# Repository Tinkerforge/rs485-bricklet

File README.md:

# rs485-bricklet
Communicates with RS485 devices

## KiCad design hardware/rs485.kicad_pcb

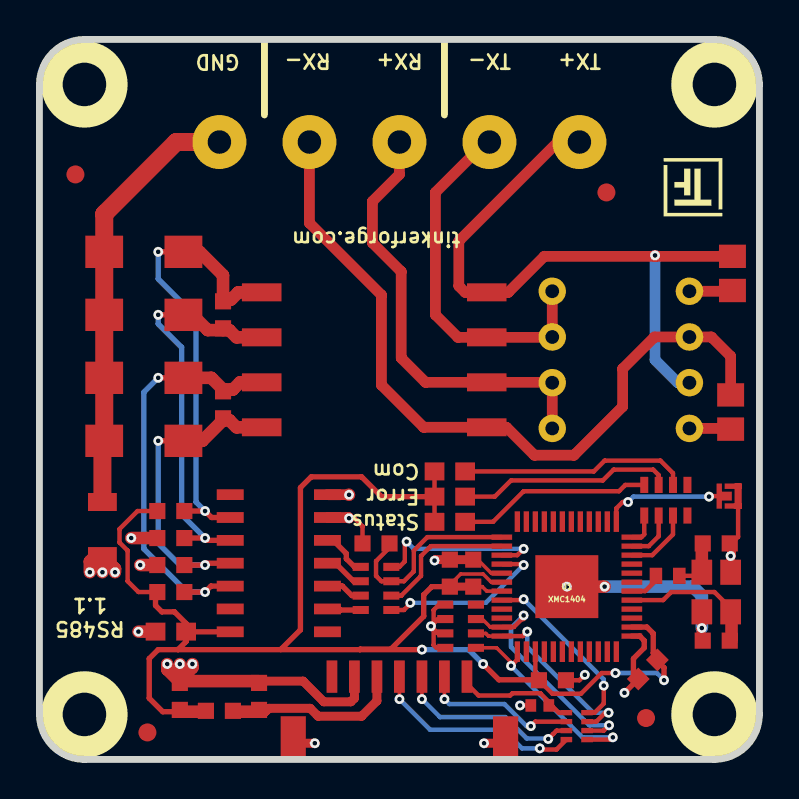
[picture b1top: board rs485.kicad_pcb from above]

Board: 2 copper layers, 40.0 x 40.0 mm, 51 parts (0 on the bottom side), 40 nets.

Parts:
C1, C2: 1uF; C0603F
C3, C4, C5: 100nF; C0603F
C6: 220nF; C0603F
C7: 100nF; C0603E
C8, C9: 10pF; C0603F
C101: 220pF; C0402F
D1: yellow; D0603E
D2: red; D0603E
D3: blue; D0603E
D4, D5, D6, D7: SMAJ24CA; DO-214AC
FB1: FILTER; R0603F
Fiducial_Mark: VAL**; Fiducial_Mark
Fiducial_Mark#2, Fiducial_Mark#3, Fiducial_Mark#4: VAL**; Fiducial_Mark
L1: WE-SL
P1: CON-SENSOR2
P2: BOOT; SolderJumper
P3: CONN_5; AKL_5_5
PTC1: 0ZCJ0016FF2E; C1206
R1, R2: 120; R0805E
R3, R5, R6, R8: 2.7k; R0603F
R4, R7: 2.2k; R0603F
R9: 0; R0402E
R101: 10k; R0603F
RP1: 1k; 0603X4
RP2, RP3: 10k; 0603X4
RP101: 82; 4X0402
SW1: SW_DIP_4; SW_DIP_4_THT
U1: XMC1404; QFN48-EP2
U2, U3, U4, U5: DRILL; DRILL_NP
U6: SP3491; SOIC-14_3.9x8.7mm_Pitch1.27mm
VAL: WEEE_7mm
VAL#2: CE_5mm
X1: 16MHz; CRYSTAL_3225

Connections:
485-D: RP2.4, U1.15
485-DE: R101.1, RP2.3, U1.13
485-R: RP2.1, U1.16
485-~REB: RP2.2, U1.14
Earth: D4.2, D5.2, D6.2, D7.2, P3.1, PTC1.1
GND: C1.1, C2.1, C3.2, C4.2, C5.2, C6.2, C7.1, C8.2, C9.2, C101.2, P1.2, P1.EP, P2.1, PTC1.2, R5.2, R8.2, R101.2, RP3.5, RP3.6, RP3.7, RP3.8, U1.17, U1.37, U1.EP, U6.6, U6.7, X1.3
unnamed: C1.2, FB1.1, P1.3
unnamed: C8.1, U1.41, X1.2
unnamed: C9.1, R9.2, X1.1
unnamed: C101.1, P1.7, RP101.5
unnamed: D1.2, RP1.2
unnamed: D2.2, RP1.3
unnamed: D3.2, RP1.4
unnamed: D4.1, L1.4, R4.2, R5.1, U6.11
unnamed: D5.1, L1.2, R7.2, R8.1, U6.10
unnamed: D6.1, L1.3, R3.2, R4.1, U6.12
unnamed: D7.1, L1.1, R6.2, R7.1, U6.9
unnamed: P1.4, RP101.8
unnamed: P1.5, RP101.7
unnamed: P1.6, RP101.6
unnamed: P2.2, U1.1
unnamed: R1.1, SW1.5
unnamed: R2.2, SW1.8
unnamed: R9.1, U1.42
unnamed: RP1.5, U1.48
unnamed: RP1.6, U1.47
unnamed: RP1.7, U1.46
unnamed: RP2.5, U6.5
unnamed: RP2.6, U6.4
unnamed: RP2.7, U6.3
unnamed: RP2.8, U6.2
RX: L1.6, P3.3, SW1.3, SW1.4
S-CLK: RP3.3, RP101.2, U1.23
S-CS: RP3.1, RP101.1, U1.25
S-MISO: RP101.4, U1.20
S-MOSI: RP3.2, RP101.3, U1.24
TX: L1.8, P3.5, R2.1, SW1.6
VCC: C2.2, C3.1, C4.1, C5.1, C6.1, C7.2, D1.1, D2.1, D3.1, FB1.2, R3.1, R6.1, U1.18, U1.19, U1.27, U1.38, U6.14
~RX: L1.5, P3.2, R1.2, SW1.7
~TX: L1.7, P3.4, SW1.1, SW1.2

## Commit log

2016-11-07 initial commit: change README
2016-11-11 routing and schematic finished, bottom markings missing
2016-11-11 add wee, ce logos, dip description, fiducials
2016-11-11 ordered first prototype
2016-11-15 add xmc1400 datasheet
2016-11-17 Add initial software implementation for RS485
    General half-duplex rx/tx wors, no TFP communication yet
2016-11-17 Add .gitignore
2016-11-22 Add implementation of first messages
2016-11-22 Add get uid bootloader function
2016-11-22 Add communication tick call
2016-11-22 Fix typo
2016-11-22 Add apply configuration prototype
2016-11-22 Add configuration enums and defines
2016-11-22 Add proper configuration and error/overrun error detection
2016-11-22 Add RXA interrupt and sort priorities properly
2016-11-22 specify crystal and capacitors
2016-11-22 Add led_flicker.c to Makefile
2016-11-22 Change priority back (RS485 only needs 3 levels)
2016-11-22 Add handling for red and yellow LED
    TODO: User LED configuration
2016-11-22 Use external oscillator
2016-11-23 Use communication callback utility function to handle callbacks
2016-11-25 Optimize tff irq handler
2016-11-25 Use error count instead of error flag, add led config
2016-11-25 Add error count and led status to struct
2016-11-25 Add API for led config and error count
2016-11-28 fix footprints
2016-11-28 Define max baudrate as 2000000 (we don't use the theoretical maximum)
2016-11-29 Add some test scripts
2016-11-29 add init
2016-11-29 Fix end of ringbuffer
2016-11-29 Add boot pad pin
2016-11-29 Add full-duplex support
2016-11-30 Use enumerate for flashing
2016-11-30 Changes in test scripts
2016-12-01 Add support for heartbeat led flicker
2016-12-02 Remove debug output
2016-12-02 Disable interrupts during buffer init
2016-12-08 Start version with 2.0.0
2016-12-08 Use clock calibration with external clock
2016-12-08 Simplify callback handling
2017-01-04 add comcu icon
2017-01-10 change bricklet connector to 7pole JST GH connector
2017-01-12 add pulldown resistors for SPI
2017-01-12 add pulldown for spi inputs, change via size
2017-01-12 change via diameter
2017-01-19 Add EEPROM emulation size
2017-01-19 Add bootloader eeprom flash read/write defines
2017-01-23 Fix include guard
2017-01-25 Add documentation related to Modbus
2017-02-03 Use O2 optimization for RS485
2017-02-07 add license file
2017-02-09 Implementation of Modbus slave read coils function. Note that this commit is not compatible with current Git brickv and bindings this will be fixed soon after timing changes are committed
2017-02-09 Add support for CCU4 based 3.5 char timer
2017-02-16 Implementation of Modbus read coils function
2017-02-21 Fix data type of read/write holding register functions
2017-02-22 Add support for Modbus write single coil function
2017-02-22 Add support for Modbus read single register function
2017-02-22 Add support for Modbus write single register function
2017-02-24 Add Modbus write multiple coils functionality
2017-02-27 Add Modbus function write multiple registers
2017-02-27 Modbus add read discrete inputs function
2017-02-28 Add Modbus function read input registers
2017-02-28 Support broadcast frame handling
2017-02-28 Fix broadcast message handling
2017-03-01 Get rid of apply_configuration() function which is not needed
2017-03-10 Adapt to bootloader LED flicker config change
2017-03-13 Use CRC16 with lookup-table
2017-04-06 Whitespace
2017-04-07 Adapt to API changes
    Add Master/Slave prefix to Modbus functions.
    Remove data parameters from Answer Write functions.
    Ensure that the normal RS485 functions do nothing in Modbus mode.
    Remove static modifier from local varaibles that don't need to be static.
2017-04-10 Broadcast for read requests are considered invalid
2017-04-10 Generate callbacks locally for broadcast write requests
2017-04-12 Add rx/tx information to allow for hald-fuplex bootstrapper flashing
2017-04-12 In slave mode write requests are answered by copying the request frame from the RX buffer
2017-04-12 Fix function parameter data type
2017-04-13 Adapt firmware for new bool array data type
2017-04-13 Use right variable
2017-04-19 Add streaming support for raw RS485 mode read/write functions
2017-04-19 bricklet-rs485: Initialize callback data
2017-04-19 Adjust streaming read callback handling
2017-04-20 Get rid of redundant count parameter
2017-04-20 Enhance error counting and timeout reporting
2017-04-21 Read function returns available data when read callback is disabled
2017-04-24 In case of a buffer overflow after reading and throwing away data instead of returning from the function continue reading as long as there is data available like in non-overflow case
2017-04-24 Ensure that in no situation unassigned values are returned through response
2017-05-02 Fix streaming read implementation
2017-05-05 Add 3d information
2017-05-05 Add 3d model: *.step & *.FCStd
2017-05-10 Fix write multiple registers endianness problem
2017-05-10 Get rid of redundant count parameter from write multiple coils/registers callbacks
2017-05-10 Change stream chunk data size to utilize all available space per packet
2017-05-10 bricklet-rs485: Change Modbus protocol level data addressing scheme
2017-05-15 Add loopback example in C and Python
2017-05-16 Make read callback to properly stream data
2017-05-17 Increase starting address for write single coil/register request callbacks
2017-05-17 Add C Modbus master and slave examples
2017-05-17 Use Modbus exception code constants
2017-05-17 Simplify Modbus master and slave mode C examples
2017-05-17 Add Modbus master and slave Python examples
2017-05-17 Add Modbus master and slave C# examples
2017-05-17 Add Modbus master and slave Ruby examples
2017-05-17 Add Modbus master and slave Java examples
2017-05-18 Fix comments
2017-05-18 Add Modbus master and slave PHP examples
2017-05-18 Add Modbus master and slave VB.NET examples
2017-05-19 Put rx and tx callback into ram for faster function call
2017-05-22 Add Modbus master and slave examples for Shell bindings
2017-05-22 Add Modbus master and slave Perl examples
2017-05-22 Add Modbus master and slave JavaScript examples
2017-05-22 Use 16 bit fifo trigger for rx interrupt
2017-05-22 Fix comment
2017-05-22 Move variable
2017-05-22 Use copy of pointer for interrupt (bettter efficiency)
2017-05-23 Fix C examples
2017-05-23 Add Modbus master and slave Delphi/Lazarus examples
2017-05-23 Fix Modbus master Ruby example
2017-05-23 Add loopback Ruby example
2017-05-24 Add Modbus master and slave MATLAB examples
2017-05-24 Add shell loopback example
2017-05-24 Fix Modbus master MATLAB example
2017-05-24 Add Modbus master and slave Octave examples
2017-05-24 Add PHP loopback example
2017-05-24 Add Perl loopback example
2017-05-24 Fix Modbus master and slave JavaScript web examples
2017-05-24 Add JavaScript loopback examples
2017-05-24 Fix loopback example comment
2017-05-24 Add Java loopback example
2017-05-24 Add C# loopback example
2017-05-24 Fix Java loopback example
2017-05-24 Add Delphi/Lazarus loopback example
2017-05-26 Fix Modbus master and slave Octave examples
2017-05-26 Fix Modbus Octave example type specifiers
2017-05-26 Add MATLAB and Octave loopback examples
2017-05-26 Add VB.NET loopback example
2017-05-26 Rename C# .NET examples
2017-06-01 c: Add missing string.h include
2017-06-01 c: Fix strndup for real now
2017-06-01 c: strndup not available with mingw32-gcc on Ubuntu 14.04
2017-06-02 Whitespace and typos
2017-06-06 Adapt examples to be more in line with the RS232 examples
    Also do some style unification.
2017-06-06 Swap mode constants
2017-06-14 php: Explode doesn't work with an empty delimiter
2017-06-23 perl: Fix array passing
2017-06-28 vbnet: Fix compile errors
2017-07-17 perl: Cleanup shared usage
2017-07-17 shell: Fix slave address in example
2017-07-17 perl: Fix shared warning
2017-07-24 examples: Add missing full-duplex configuration
2017-07-25 Add Mathematica examples
2017-07-25 Add LabVIEW examples
2017-07-26 add schematic file
2017-07-27 Update changelog
2017-08-24 Specify R9 to 0 Ohm
2017-08-30 Fix bug: starting address was not being adjusted for multi-chunk streams
2017-08-30 Fix version
2017-09-08 fix footprint silkscreen layers
2017-10-20 Java: Fix example
2017-11-17 delphi: Fix example
2017-11-17 delphi,javascript: Disable streaming example until streaming is fully supported
2017-11-30 @{function_camel_case_name}[
2017-11-30 Update examples from generator
2017-12-06 specify new rs485 biasing resistors
2017-12-07 mathematica: Also generate .nb files
2018-01-30 vbnet: Update print format
2018-02-19 javascript: Close div tag correctly
2018-02-20 Cleanup KiCad libraries config
    Ensure LibDir=kicad-libraries and LibName1=tinkerforge.
    Remove special library.
2018-02-22 delphi: Fix syntax error
2018-03-05 Remove unused flash-size define
2018-05-24 perl: Use strict in examples
2018-06-28 Fix readme
2018-07-11 Add Makefile with docker support
2018-07-11 Update directory structure and build instructions
2018-07-11 Remove obsolete generate_makefile scripts
2018-07-17 delphi: Use PChar instead of PAnsiChar
    With PAnsiChar the message "test" will be printed as "t e " in Delphi XE.
2018-07-17 ruby: Remove redundant parentheses
2018-10-04 Increase version for new release (changes in bricklib2)
2018-10-04 Add rev to changelog
2018-11-05 Fixed size of response for modbus master write single register function
2018-11-06 Fix response length for modbus_master_write_single_coil function
    Reponse was too long before and API bindings just ignored extra data.
2018-11-06 Increase version number
2018-11-06 Add commit ref
2018-11-06 Add rust examples
2018-11-07 rust: Accept host names for ip connection, fix naming inconsistencies
2018-11-07 rust: Rename callback receivers.
2018-12-14 Add go examples.
2018-12-18 go: Change import path.
2018-12-18 go: Change import path again.
2018-12-20 rust: Reformat examples.
2018-12-21 ruby: Fix modbus master example.
2019-01-24 mqtt: Add examples.
2019-01-24 mqtt: Remove executable bit in example permissions.
2019-01-24 go: Minor example fixes.
2019-01-24 mqtt: Add modbus examples.
2019-05-24 Add special Ambient Light over Modbus example
2019-08-22 c: Adapt to bindings changes
2020-01-14 examples: Use python3 input by default.
2020-02-13 Don't reset stream in getter if callback is enabled and vice versa.
2020-02-17 Add frame readable callback.
2020-02-24 Fix word length != 8.
2020-02-25 Add get_frame_readable_callback_configuration.
2020-02-25 Mutually exclude read/frame_readable callbacks.
2020-02-27 fix weee logo
2020-02-28 Append to changelog.
2020-02-28 Add commit ref to changelog.
2020-03-18 examples: Minor cleanups
2020-03-23 specify processor
2020-04-03 Add openHAB examples.
2020-08-19 Add uc examples.
2020-08-25 uc: Adapt exampleS to new skeleton
2020-08-27 uc: Fix warnings.
2020-08-31 uc: Use fixed-with placeholders in format strings.
2020-09-02 uc: Add example driver note.
2020-10-30 python: Workaround pylint warning
2021-03-26 version 1.1
    change SPI filter design
2021-03-26 update stuff
2021-03-30 add DE pulldown
2021-10-11 Fix (theoretical) buffer overflow in modbus checksum calculation
    and fix uint16 alignment problem
2021-10-11 Add rev for 2.0.6
2021-10-25 Update KiCad link
    https://www.kicad.org/blog/2021/10/Avoid-links-to-former-kicad-domain/
2022-04-19 examples: uc: Rename TF_HalContext to TF_HAL.
2022-04-26 uc: Adapt to bindings changes
2022-06-22 specify part
2022-07-06 Add license files.
2025-10-04 Fix compatibility with new Docker build image (GCC 14.2.1)

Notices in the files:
hardware/rs485.kicad_pcb:
Licensed under CERN OHL v.1.1
Copyright (©) 2021, B.Nordmeyer
Copyright Tinkerforge GmbH 2021.
This documentation describes Open Hardware and is licensed under the
CERN OHL v. 1.1.
